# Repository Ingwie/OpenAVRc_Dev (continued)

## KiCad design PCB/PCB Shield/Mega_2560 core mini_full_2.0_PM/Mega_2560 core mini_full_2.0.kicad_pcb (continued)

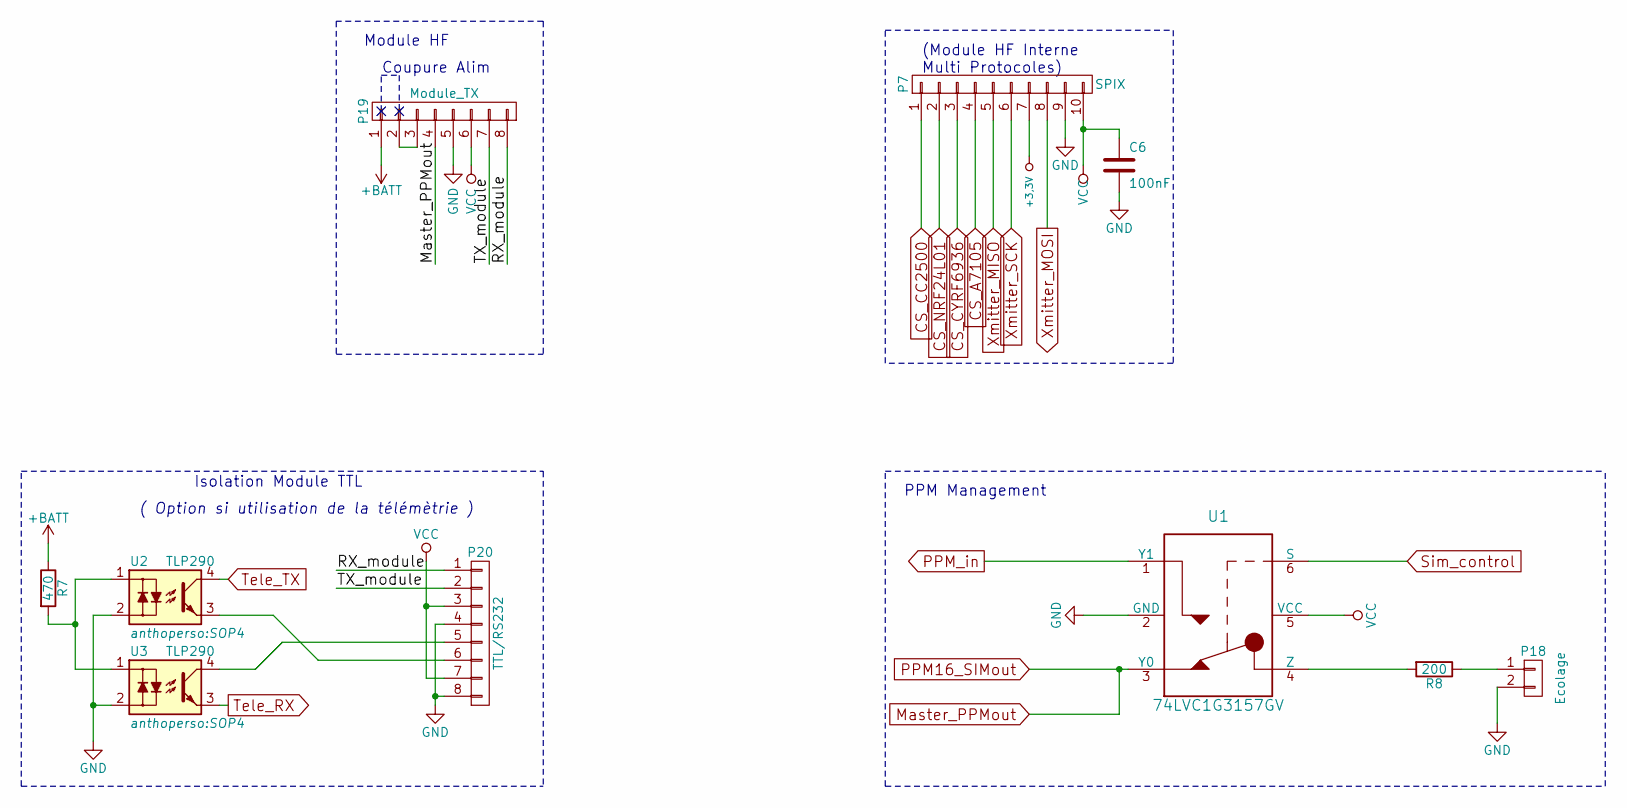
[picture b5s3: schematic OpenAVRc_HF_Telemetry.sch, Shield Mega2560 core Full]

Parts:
C6: 100nF; C_1206
P7: SPIX; Pin_Header_Straight_2x05_Pitch2.54mm
P18: Ecolage; Pin_Header_Straight_1x02_Pitch2.54mm
P19: Module_TX; Pin_Header_Straight_2x04_Pitch2.54mm
P20: TTL/RS232; Con_RS232_TTL
R7: 470; R_1206
R8: 200; R_1206
U1: 74LVC1G3157GV; SOT-457
U2, U3: TLP290; SOP4

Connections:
+3.3V: P7.7; also elsewhere on the board
/OpenAVRc_HF_Telemetry/RX_module: P19.8, P20.1
/OpenAVRc_HF_Telemetry/TX_module: P19.7, P20.2
CS_A7105: P7.4; also elsewhere on the board
CS_CC2500: P7.1; also elsewhere on the board
CS_CYRF6936: P7.3; also elsewhere on the board
CS_NRF24L01: P7.2; also elsewhere on the board
GND: C6.2, P7.9, P18.2, P19.5, P20.4, P20.8, U1.2 (GND), U2.2, U3.2; also elsewhere on the board
Master_PPMout: P19.4; also elsewhere on the board
unnamed: P18.1, R8.1
unnamed: P19.2, P19.3
unnamed: P20.5, U3.4
unnamed: P20.6, U2.3
unnamed: R7.2, U2.1, U3.1
unnamed: R8.2, U1.4 (Z)
PPM16_SIMout: U1.3 (Y0); also elsewhere on the board
PPM_in: U1.1 (Y1); also elsewhere on the board
Sim_Control: U1.6 (S); also elsewhere on the board
Tele_RX: U3.3; also elsewhere on the board
Tele_TX: U2.4; also elsewhere on the board
VCC: C6.1, P7.10, P19.6, P20.3, P20.7, U1.5 (VCC); also elsewhere on the board
Xmitter_MISO: P7.5; also elsewhere on the board
Xmitter_MOSI: P7.8; also elsewhere on the board
Xmitter_SCK: P7.6; also elsewhere on the board

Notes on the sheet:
Isolation Module TTL
PPM Management
( Option si utilisation de la télémètrie )
Coupure Alim
Module HF
(Module HF Interne Multi Protocoles)

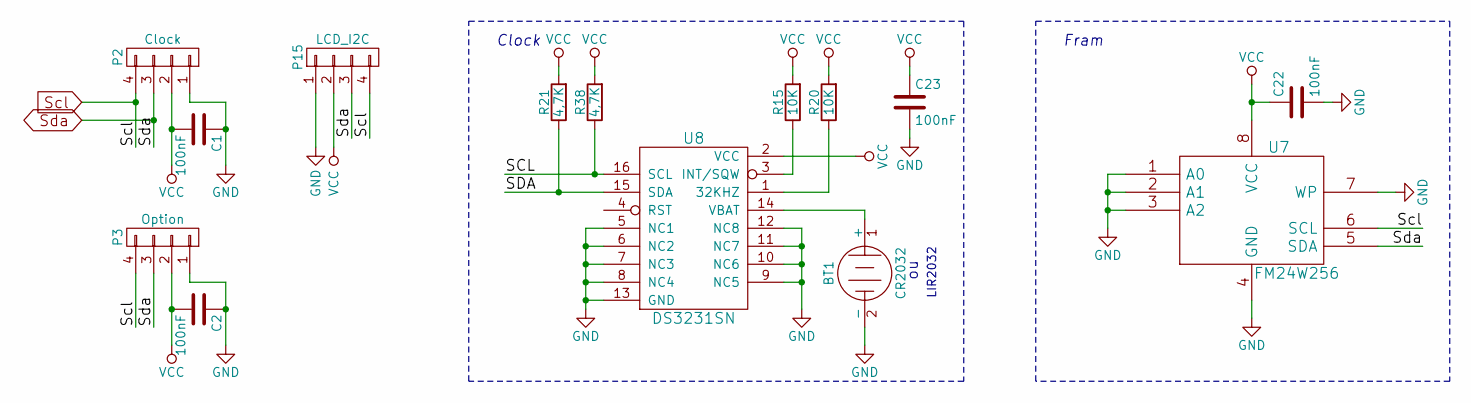
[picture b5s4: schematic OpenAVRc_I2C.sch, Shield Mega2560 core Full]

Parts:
BT1: CR2032; Pin_Header_Straight_1x02_Pitch2.54mm
C1, C2, C22, C23: 100nF; C_1206
P2: Clock; Pin_Header_Straight_1x04_Pitch2.54mm
P3: Option; Pin_Header_Straight_1x04_Pitch2.54mm
P15: LCD_I2C; Pin_Header_Straight_1x04_Pitch2.54mm
R15, R20: 10K; R_1206
R21, R38: 4,7K; R_1206
U7: FM24W256; SOIC-8-FRAM_DI
U8: DS3231SN; SO-16-DS3231

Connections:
GND: BT1.2 (-), C1.1, C2.1, C22.2, C23.2, P2.1, P3.1, P15.1, U7.1 (A0), U7.2 (A1), U7.3 (A2), U7.4 (GND), U7.7 (WP), U8.5 (NC1), U8.6 (NC2), U8.7 (NC3), U8.8 (NC4), U8.9 (NC5), U8.10 (NC6), U8.11 (NC7), U8.12 (NC8), U8.13 (GND); also elsewhere on the board
unnamed: BT1.1 (+), U8.14 (VBAT)
unnamed: R15.1, U8.3 (INT/SQW)
unnamed: R20.1, U8.1 (32KHZ)
Scl: P2.4, P3.4, P15.4, R38.1, U7.6 (SCL), U8.16 (SCL); also elsewhere on the board
Sda: P2.3, P3.3, P15.3, R21.1, U7.5 (SDA), U8.15 (SDA); also elsewhere on the board
VCC: C1.2, C2.2, C22.1, C23.1, P2.2, P3.2, P15.2, R15.2, R20.2, R21.2, R38.2, U7.8 (VCC), U8.2 (VCC); also elsewhere on the board

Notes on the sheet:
Clock
Fram
LIR2032

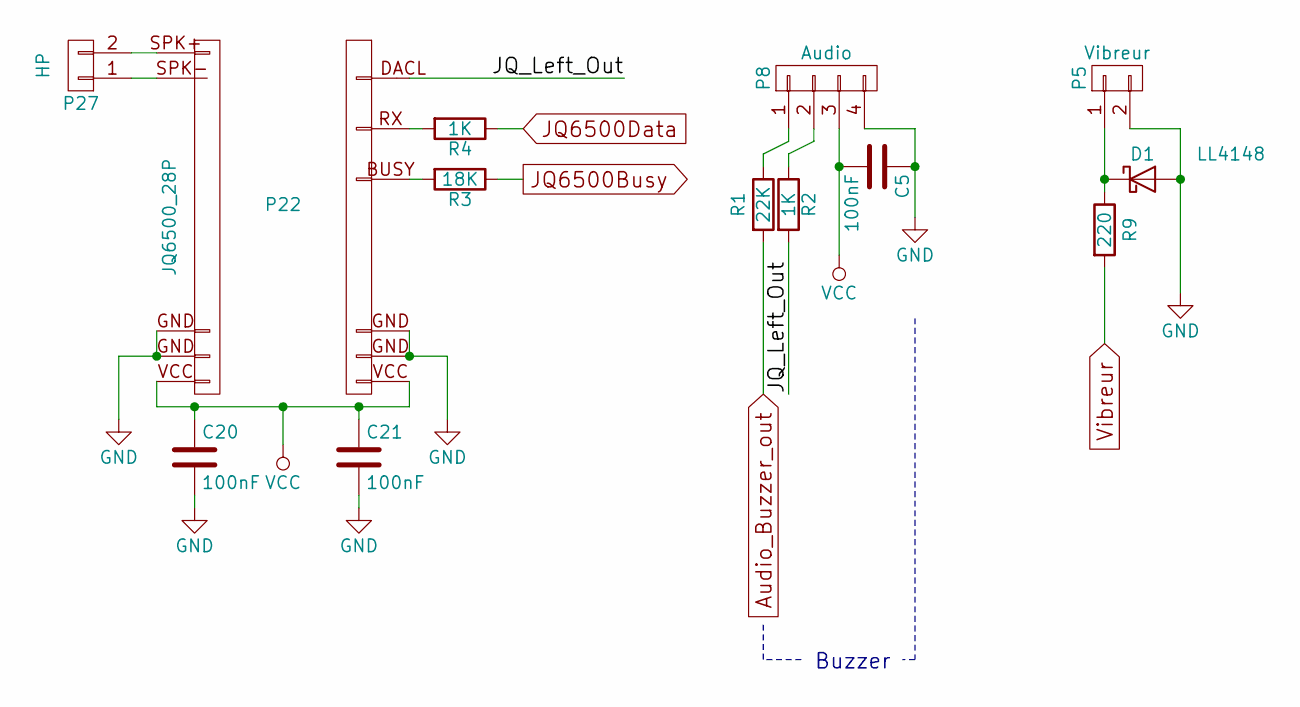
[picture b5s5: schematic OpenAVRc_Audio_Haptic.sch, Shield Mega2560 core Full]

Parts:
C5, C20, C21: 100nF; C_1206
D1: LL4148; D_SOD-123
P5: Vibreur; Pin_Header_Straight_1x02_Pitch2.54mm
P8: Audio; Pin_Header_Straight_1x04_Pitch2.54mm
P22: JQ6500_28P; connector_mini-JQ6500-28P
P27: HP; Pin_Header_Straight_1x02_Pitch2.54mm
R1: 22K; R_1206
R2, R4: 1K; R_1206
R3: 18K; R_1206
R9: 220; R_1206

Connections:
/OpenAVRc_Audio_Haptic/JQ_Left_Out: P22.DACL (P16), R2.2; also elsewhere on the board
Audio_Buzzer_out: R1.2; also elsewhere on the board
GND: C5.1, C20.2, C21.2, D1.2 (A), P5.2, P8.4, P22.GND (P12); also elsewhere on the board
JQ6500Busy: R3.1; also elsewhere on the board
JQ6500Data: R4.1; also elsewhere on the board
unnamed: D1.1 (K), P5.1, R9.1
unnamed: P8.1, R1.1
unnamed: P8.2, R2.1
unnamed: P22.BUSY (P20), R3.2
unnamed: P22.RX (P18), R4.2
unnamed: P22.SPK+ (P1), P27.2
unnamed: P22.SPK- (P2), P27.1
VCC: C5.2, C20.1, C21.1, P8.3, P22.VCC (P14); also elsewhere on the board
Vibreur: R9.2; also elsewhere on the board

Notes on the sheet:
Buzzer

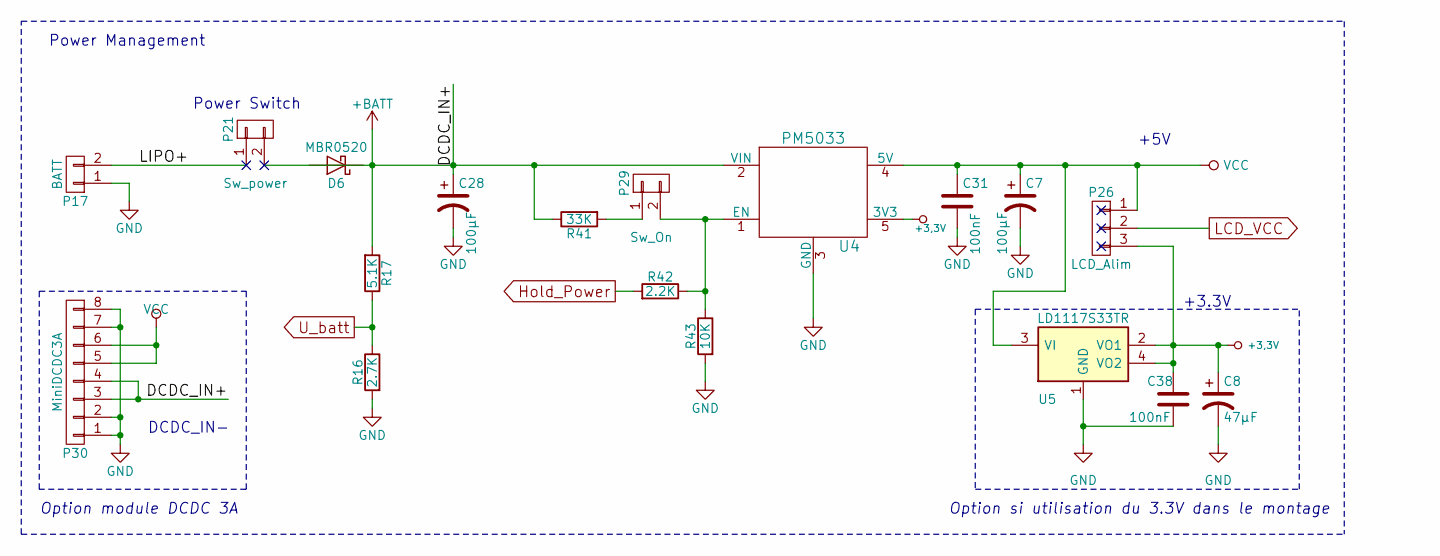
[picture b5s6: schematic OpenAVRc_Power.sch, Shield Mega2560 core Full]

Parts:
C7, C28: 100µF; CP_Elec_6.3x5.3
C8: 47µF; CP_Elec_6.3x5.3
C31, C38: 100nF; C_1206
D6: MBR0520; D_SOD-123
P17: BATT; Pin_Header_Straight_1x02_Pitch2.54mm
P21: Sw_power; Pin_Header_Straight_1x02_Pitch2.54mm
P26: LCD_Alim; Pin_Header_Straight_1x03_Pitch2.54mm
P29: Sw_On; Pin_Header_Straight_1x02_Pitch2.54mm
P30: MiniDCDC3A
R16: 2.7K; R_1206
R17: 5.1K; R_1206
R41: 33K; R_1206
R42: 2.2K; R_1206
R43: 10K; R_1206
U4: PM5033; PM5033_SIL5
U5: LD1117S33TR; SOT-223

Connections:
+3.3V: C8.1, C38.1, P26.3, U4.5 (3V3), U5.2 (VO1), U5.4 (VO2); also elsewhere on the board
/OpenAVRc_Power/LIPO+: P17.2, P21.1
GND: C7.2, C8.2, C28.2, C31.2, C38.2, P17.1, P30.1, P30.2, P30.7, P30.8, R16.2, R43.2, U4.3 (GND), U5.1 (GND); also elsewhere on the board
Hold_Power: R42.2; also elsewhere on the board
LCD_VCC: P26.2; also elsewhere on the board
unnamed: P29.1, R41.2
unnamed: P29.2, R42.1, R43.1, U4.1 (EN)
U_batt: R16.1, R17.1; also elsewhere on the board
VCC: C7.1, C31.1, P26.1, P30.5, P30.6, U4.4 (5V), U5.3 (VI); also elsewhere on the board

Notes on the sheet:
+3.3V
+5V
Power Management
Option si utilisation du 3.3V dans le montage
Power Switch
DCDC_IN-
Option module DCDC 3A

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
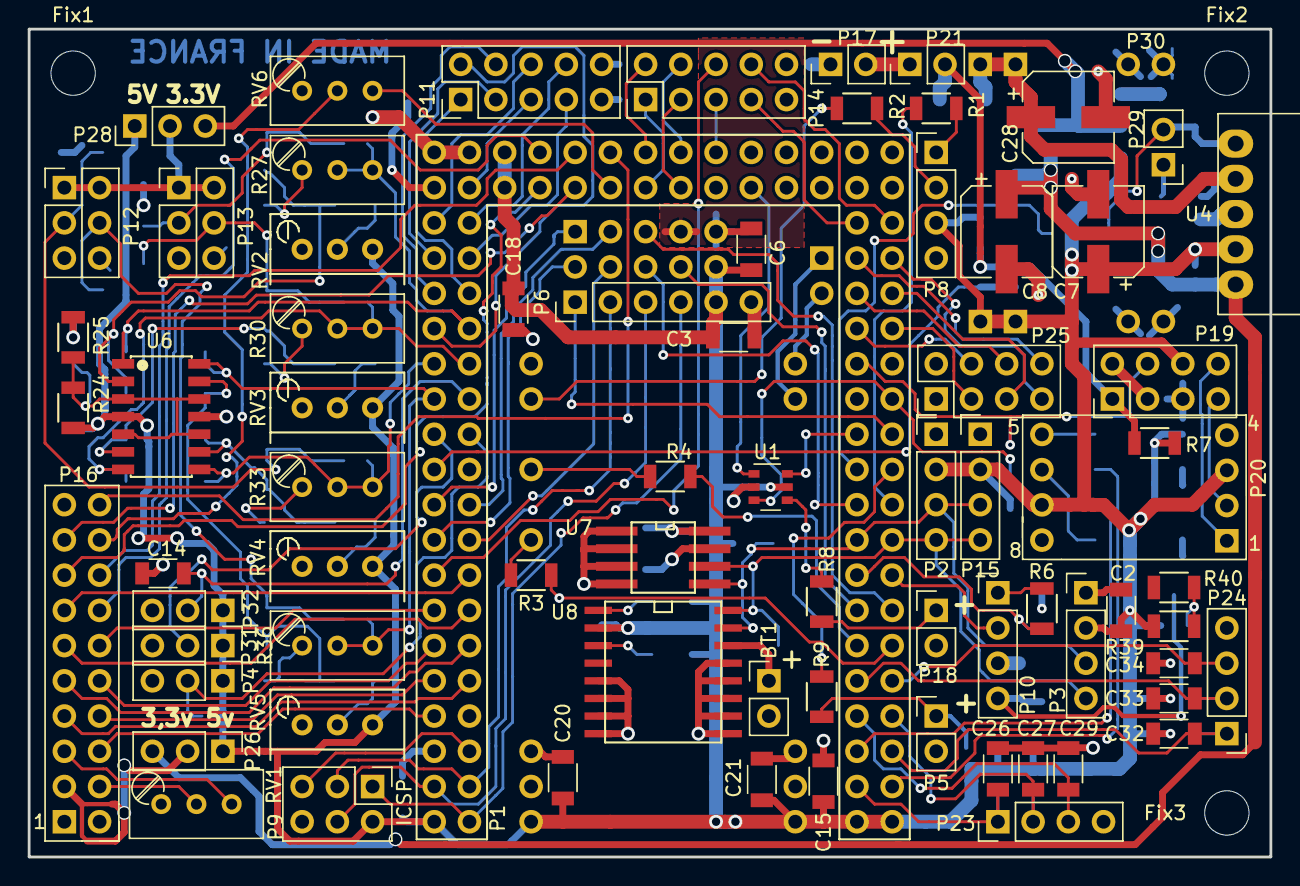
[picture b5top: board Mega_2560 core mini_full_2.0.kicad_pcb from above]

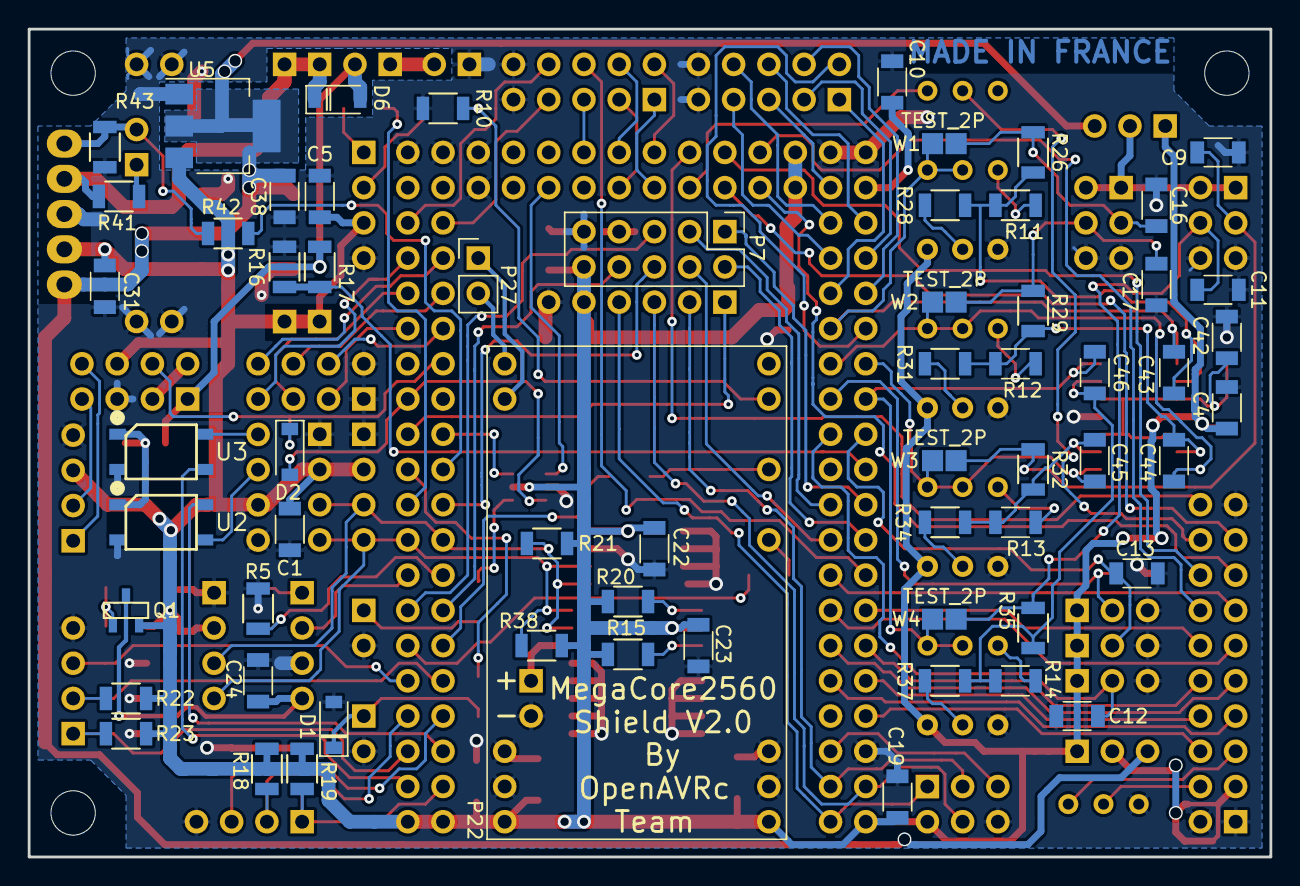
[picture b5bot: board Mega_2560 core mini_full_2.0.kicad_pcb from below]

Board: 2 copper layers, 89.5 x 59.7 mm, 139 parts (62 on the bottom side), 130 nets.

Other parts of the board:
D2: MBR0520; D_SOD-123
Fix1, Fix2, Fix3: MountingHole_3.2mm_M3
R10: 22K; R_1206
R18, R19, R22, R23: 5.1K; R_1206

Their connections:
/OpenAVRc_Audio_Haptic/JQ_Left_Out: R10.1; also elsewhere on the board
GND: R10.2; also elsewhere on the board
Master_PPMout: D2.1; also elsewhere on the board
PPM16_SIMout: D2.2; also elsewhere on the board
Rot_1B: R18.2; also elsewhere on the board
Rot_1push: R19.2; also elsewhere on the board
Rot_2B: R22.2; also elsewhere on the board
Rot_2push: R23.2; also elsewhere on the board
VCC: R18.1, R19.1, R22.1, R23.1; also elsewhere on the board

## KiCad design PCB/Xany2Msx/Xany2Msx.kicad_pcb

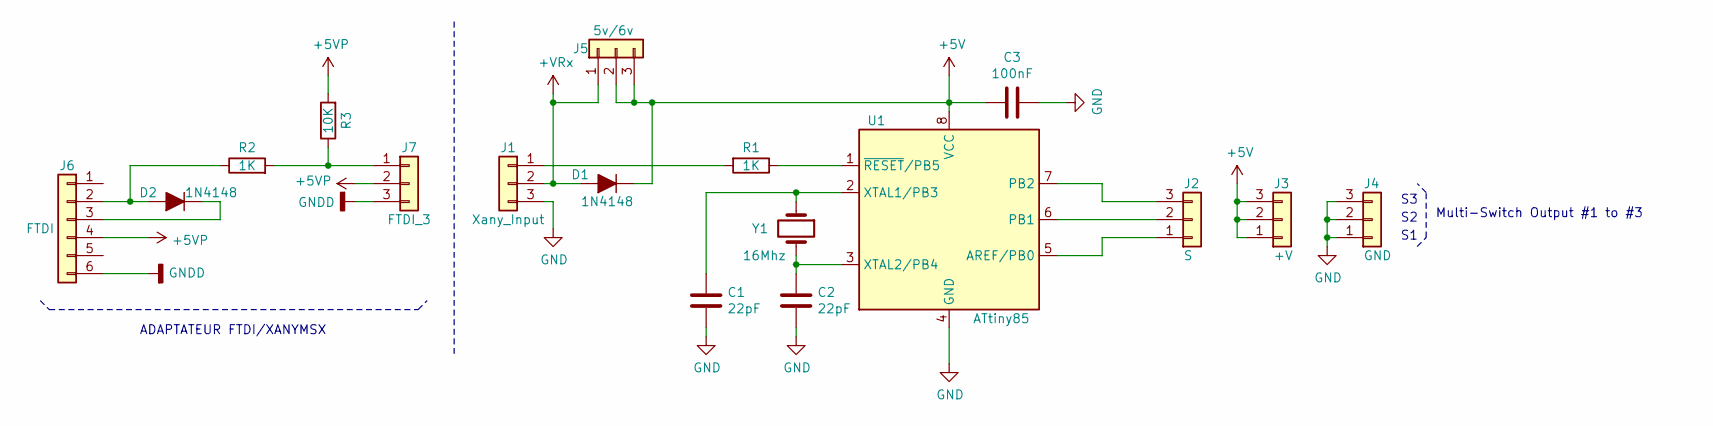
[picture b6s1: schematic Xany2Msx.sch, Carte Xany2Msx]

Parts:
C1, C2: 22pF; C_Disc_D3.0mm_W2.0mm_P2.50mm
C3: 100nF; C_Disc_D3.0mm_W2.0mm_P2.50mm
D1, D2: 1N4148; D_A-405_P2.54mm_Vertical_KathodeUp
J1: Xany_Input; Pin_Header_Straight_1x03_Pitch2.54mm
J2: S; Pin_Header_Straight_1x03_Pitch2.54mm
J3: +V; Pin_Header_Straight_1x03_Pitch2.54mm
J4: GND; Pin_Header_Straight_1x03_Pitch2.54mm
J5: 5v/6v; Pin_Header_Straight_1x03_Pitch2.54mm
J6: FTDI; Pin_Header_Straight_2x03_Pitch2.54mm
J7: FTDI_3; Pin_Header_Straight_1x03_Pitch2.54mm
R1, R2: 1K; R_Axial_DIN0204_L3.6mm_D1.6mm_P2.54mm_Vertical
R3: 10K; R_Axial_DIN0204_L3.6mm_D1.6mm_P2.54mm_Vertical
U1: ATtiny85; DIP-8_W7.62mm
Y1: 16Mhz; HC-39

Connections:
+5V: C3.2, D1.1 (K), J3.1, J3.2, J3.3, J5.2, J5.3, U1.8 (VCC)
+5VP: J6.4, J7.2, R3.2
+VRx: D1.2 (A), J1.2, J5.1
GND: C1.2, C2.2, C3.1, J1.3, J4.1, J4.2, J4.3, U1.4 (GND)
GNDD: J6.6, J7.3
unnamed: C1.1, U1.2 (XTAL1/PB3), Y1.1
unnamed: C2.1, U1.3 (XTAL2/PB4), Y1.2
unnamed: D2.1 (K), J6.3
unnamed: D2.2 (A), J6.2, R2.1
unnamed: J1.1, R1.2
unnamed: J2.1, U1.5 (AREF/PB0)
unnamed: J2.2, U1.6 (PB1)
unnamed: J2.3, U1.7 (PB2)
unnamed: J7.1, R2.2, R3.1
unnamed: R1.1, U1.1 (~RESET~/PB5)

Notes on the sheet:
Multi-Switch Output #1 to #3
ADAPTATEUR FTDI/XANYMSX

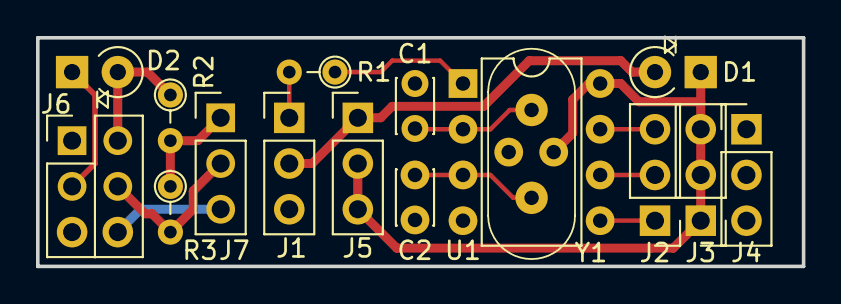
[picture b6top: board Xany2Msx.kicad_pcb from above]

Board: 2 copper layers, 42.5 x 12.7 mm, 17 parts (1 on the bottom side), 15 nets.
